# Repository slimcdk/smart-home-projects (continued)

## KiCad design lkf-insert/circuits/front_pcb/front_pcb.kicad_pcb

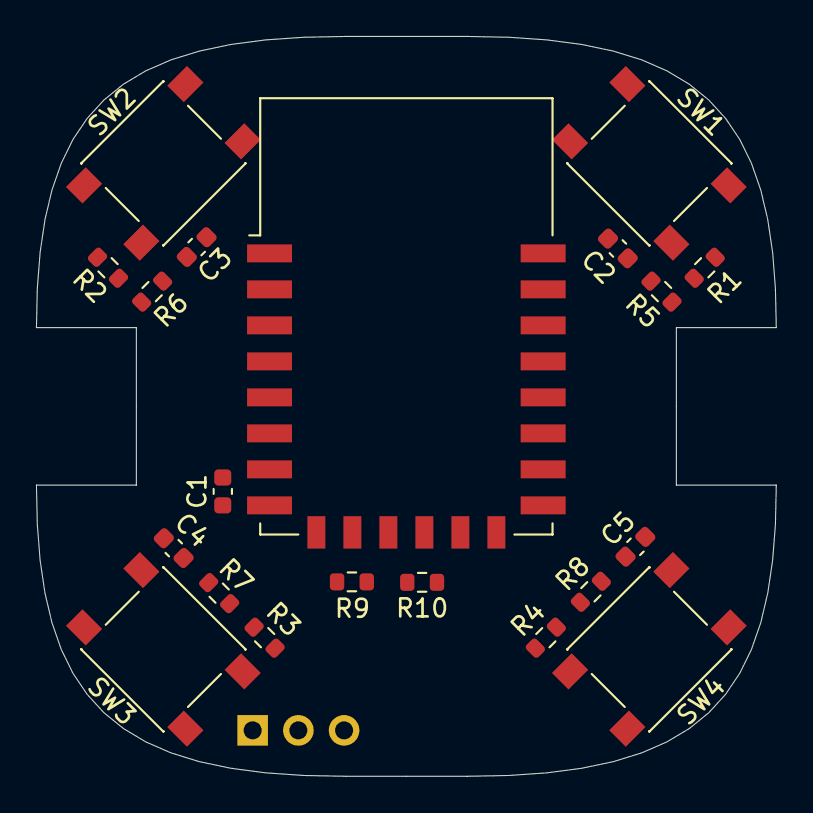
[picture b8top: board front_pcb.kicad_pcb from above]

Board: 2 copper layers, 41.1 x 41.1 mm, 21 parts (1 on the bottom side), 13 nets, no tracks yet.

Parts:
C1: 10µF; C_0603_1608Metric
C2, C3, C4, C5: 0.1µF; C_0603_1608Metric
J1: Inter_PCB_Conn; PinHeader_1x03_P2.54mm_Vertical
R1, R2, R3, R4: 1K; R_0603_1608Metric
R5, R6, R7, R8: 10K; R_0603_1608Metric
R9, R10: 10k; R_0603_1608Metric
SW1, SW2, SW3, SW4: SW_Push; SW_SPST_PTS645
U1: ESP-12F; ESP-12E

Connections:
+3V3: C1.1, J1.2, R9.2, R10.2, SW1.1, SW2.1, SW3.1, SW4.1, U1.8
/AC_PWR_CTL: J1.3, U1.19
/SW1: C2.2, R1.1, R5.1, U1.20
/SW2: C3.2, R2.1, R6.1, U1.5
/SW3: C4.2, R3.1, R7.1, U1.11
/SW4: C5.2, R4.1, R8.1, U1.12
GND: C1.2, C2.1, C3.1, C4.1, C5.1, J1.1, R5.2, R6.2, R7.2, R8.2, U1.15
unnamed: R1.2, SW1.2
unnamed: R2.2, SW2.2
unnamed: R3.2, SW3.2
unnamed: R4.2, SW4.2
unnamed: R9.1, U1.1
unnamed: R10.1, U1.3

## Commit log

2020-06-30 roller shade v0.0.0 motor mount test
2020-12-31 updates to esp roller shades
2020-12-31 updates to many projects
2021-01-03 refractored repository
2021-01-03 resolved nested repository tracking
2021-01-03 added some readmes
2021-01-09 trv updates
2021-01-09 work on LK Fuga insert
2021-01-09 refractoring
2021-01-10 work on LK Fuga
2021-01-10 refractored and organized repository
2021-01-10 export directory for four switch insert
2021-01-15 a lot of changes
2021-01-18 added some openscad libaries
2021-01-18 new base for aurora
2021-01-19 added cad libaries (submodules)
2021-01-19 working on new design for roller shades
2021-01-19 added housing for environment sensor
2021-01-19 tiny updates to LK insert
2021-01-21 added NopSCADlib
2021-02-02 renamed trv project
2021-02-02 renamed water bottle project
2021-02-02 simplified aurora base
2021-02-02 discarded glowing rock project
2021-02-02 work on chain string based drivetrain for roller shades
2021-02-02 projects updates
2021-02-02 LKF 4-ESP rename and modelling in FreeCAD
2021-02-02 Readme update
2021-02-06 Working on roller shades
2021-02-08 refractored repository once again with additional changes to some projects
2021-02-08 removed exported test models and some openscad code
2021-02-11 Refractored KiCAD repo libraries and added AS5601-ASOM
2021-02-12 reworked frame for smart mirror including test prints
2021-02-13 Test printing mirror frame
2021-02-15 work on roller shade schmatics
2021-02-15 Empty FreeCAD projects
2021-02-22 work on lkf insert using kicad and freecad synergy
2021-02-22 added a few new dependencies
2021-02-22 working on driver board using kicad stepup for freecad
2021-02-22 deleted test print files
2021-02-22 added two new small projects; bed foor and bed light
2021-02-26 LKF insert front pcb missing tracing; ready to order
2021-02-26 adjusted bolt clearance on bed foot
2021-02-26 lkf series pcbs traced and mostly ready for order
2021-02-27 some lkf images
2021-03-10 unified repository kicad dependencies
2021-03-10 started on schmatics and proper cad model
2021-03-10 layout for NEMA17 backpack driver board
2021-03-10 many changes to lkf-series project
2021-03-10 work on proper cad model and schmatics
2021-03-10 working on more assembly friendly version of smart mirror
2021-05-18 Adding Halo Clock project files
2021-05-18 Updated readme for halo clock
2021-05-18 Updated readme for halo clock once again
2021-05-18 Work on esp ceiling spot
2021-05-18 Updated Auroro project files
2021-05-18 Renamed Halo Clock CAD files
2021-05-18 Refractored, deleted and archived a few projects
2021-05-18 Refractored dependencies into each project and added missing folders
2021-05-18 Added descriptions to halo clock readme
2021-05-18 Added a new line character
2021-05-18 Fixed a link reference and title
2021-05-18 Fixed title for roller shades
